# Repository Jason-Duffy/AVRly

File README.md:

# C Programming Resources for AVR MCU's
 
[Getting Started][Getting_Started_URL]

[Getting_Started_URL]: https://jason-duffy.github.io/C-Programming-Resources-for-AVR-MCU-s/getting-started/index.html

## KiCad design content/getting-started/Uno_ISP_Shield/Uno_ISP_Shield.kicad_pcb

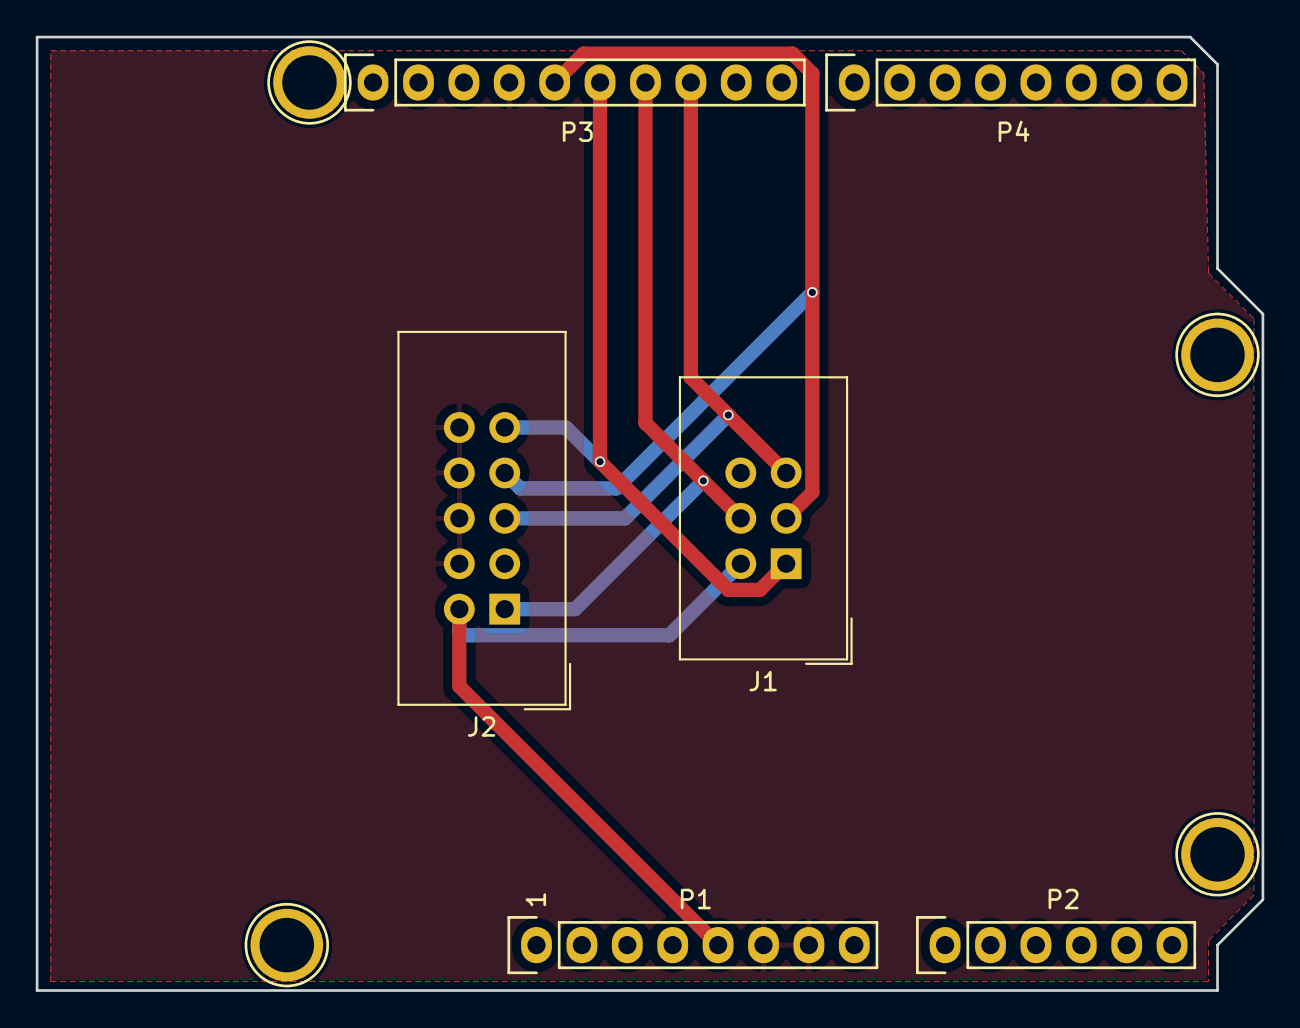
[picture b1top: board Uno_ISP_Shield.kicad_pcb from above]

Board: 2 copper layers, 68.6 x 53.3 mm, 10 parts (0 on the bottom side), 6 nets.

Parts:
J1: AVR-ISP-6; IDC-Header_2x03_P2.54mm_Vertical
J2: AVR-ISP-10; IDC-Header_2x05_P2.54mm_Vertical
P1: Power; Socket_Strip_Arduino_1x08
P2: Analog; Socket_Strip_Arduino_1x06
P3: Digital; Socket_Strip_Arduino_1x10
P4: Digital; Socket_Strip_Arduino_1x08
P5, P6, P7, P8: CONN_01X01; Arduino_1pin

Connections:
10(SS): J1.5, J2.5, P3.8
11(MOSI): J1.4, J2.1, P3.7
12(MISO): J1.1, J2.9, P3.6
13(SCK): J1.3, J2.7, P3.5
+5V: J1.2, J2.2, P1.5
GND: J1.6, J2.4, J2.6, J2.8, J2.10, P1.6, P1.7, P3.4

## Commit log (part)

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2022-03-24 docs regen
2022-03-26 Update Contributors-guide.md
    Added development process section to Contributor's guide.
2022-03-26 Edited comments to match
2022-04-02 Added links to git repo in each module description
2022-04-02 docs cleanup
2022-04-02 removed doxygen documentation
2022-04-02 edited documentation structure for module
2022-04-02 dpcs regen
2022-04-02 edited documentation structure
2022-04-02 added avr-peripheral files
2022-04-04 removed/relocated files
2022-04-04 relocated files, added demo clock functionality
2022-04-05 Added main.c with basic hello world demo
2022-04-05 Updated to new Makefile for m328p
2022-04-05 Corrected typos
2022-04-06 corrected grouping
2022-04-06 test for OCR0A value based on F_CPU defined speed
2022-04-06 Update Makefile
2022-04-06 docs
2022-04-09 Added log_system temporarily for debugging
2022-04-09 Switched to new style makefile for 328p
2022-04-09 edited pinout for 328p
2022-04-09 Corrected driver to work for all models
    Only tested on MCP4812 so far
2022-04-09 Simplified dac_reconfigure() function
    Instead of testing for model again, set a variable in the init() function and use that to shift the level variable into the correct place each time.
2022-04-09 Moved SPI setup and functions to separate module
2022-04-10 Fixed bug - SPI_SS was an unknown voltage.
2022-04-10 Added function to print 16bit decimal
2022-04-10 Added SS line
2022-04-10 removed debug logging
2022-04-10 removed debug logging
    Also moved chip_select control back to this module
2022-04-10 fixed minor documentation issue
2022-04-10 formatting fixed
2022-04-11 Tidied up comment blocks & documentation
2022-04-11 Tidied up comment block and documentation
2022-04-11 Minor correction
2022-04-11 Tidied up demo routine and documentation
2022-04-11 added SPI and I2C groups
2022-04-22 renamed file
2022-04-22 renamed groups
2022-04-22 edited grouping
2022-04-22 removed old docs
2022-04-22 added to documentation
2022-04-22 improved formatting
2022-05-01 Create Makefile
2022-05-01 Added return statement
2022-05-01 added group USART
2022-05-01 corrected link to external repo
2022-05-01 Added intro
2022-05-01 cleaned up comments
2022-05-01 replaced with higher res version
2022-05-01 Added more data type output functionality
2022-05-01 Added example routine for demo
2022-05-01 changed grouping
2022-05-01 added comments to new functions
2022-05-01 Updated to new version
2022-05-01 Updated to match new function names in usart.h
2022-05-02 Added documentation
2022-05-02 Added comments and implementation for setter functions
2022-05-02 Testing global/file scope functionality
    Global on/off and global log max level are working, about to try a new approach for file scope log level setting.
2022-05-02 Added better demonstration routine
2022-05-02 Added log level verification at global and file levels.
2022-05-02 corrected param references in documentation
2022-05-10 File renamed
2022-05-12 Edited pinout to suit atmega328p
2022-05-12 Switched to new style makefile, for 328p
2022-05-15 removed _BV() macro
2022-05-15 edited doxygen file tag
2022-05-15 cropped image
2022-06-22 Added bme280 example files
2022-06-22 added i2c driver
2022-06-22 renamed files
2022-06-24 Updated function prototypes for all integer sizes
    Also added format enum, need to update function definitions and implementations to suit.
2022-06-24 Cleaned up and removed functions no longer needed
2022-06-24 Added usart files for logger
2022-06-24 Added example for pressure and humidity logging
2022-07-10 added links
2022-07-10 Tidied up
2022-07-10 Tidied up, shortened to max 80 char wide
2022-07-10 Added BME280 module
2022-07-10 Corrected syntax error in prototypes
2022-07-10 corrected module grouping
2022-07-10 testing new logging method
2022-07-10 changed to suppress leading zeroes
2022-07-10 corrected docs comments
2022-07-10 testing negative values
2022-09-13 Added AM radio demo
2022-09-13 Temporary fix to logging subsystem
2022-09-13 Added doxygen comment blocks
2022-09-13 Update Gemfile
2022-09-13 removed old .md files
2022-09-13 updated config
2022-09-13 Added link to git repo
2022-09-14 Added HAL files for experimentation
